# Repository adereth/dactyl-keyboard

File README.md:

# The Dactyl Keyboard
The Dactyl is a parameterized, split-hand, concave, columnar, ergonomic keyboard.

This is my fork of [the original Dactyl][], with rotated thumb clusters, a steeper angle, Ergodox-compatible keycaps, and a simpler one-piece chassis.

[the original Dactyl]: https://github.com/adereth/dactyl-keyboard

There's a talk about the motivation and design of the Dactyl that helps provide context for this repo:

## Assembly

### Generating a Design

**Setting up the Clojure environment**
* [Install the Clojure runtime](https://clojure.org)
* [Install the Leiningen project manager](http://leiningen.org/)
* [Install OpenSCAD](http://www.openscad.org/)

**Generating the design**
* Run `lein repl`
* Load the file `(load-file "src/dactyl_keyboard/dactyl.clj")`
* This will regenerate the `things/*.scad` files
* Use OpenSCAD to open a `.scad` file.
* Make changes to design, repeat `load-file`, OpenSCAD will watch for changes and rerender.
* When done, use OpenSCAD to export STL files

**Tips**
* [Some other ways to evaluate the clojure design file](http://stackoverflow.com/a/28213489)
* [Example designing with clojure](http://adereth.github.io/blog/2014/04/09/3d-printing-with-clojure/)

### Printing
Pregenerated STL files are available in the [things/](things/) directory.

### Wiring
Masks for the flexible PCBs I used are available for the [left](resources/pcb-left.svg) and [right](resources/pcb-right.svg) side.

A [very rough guide for the brave is here](guide/README.org#wiring) - It will be improved over time (**TODO**)!

## License

Copyright © 2015 Matthew Adereth

The source code for generating the models (everything excluding the [things/](things/) and [resources/](resources/) directories is distributed under the [GNU AFFERO GENERAL PUBLIC LICENSE Version 3](LICENSE).  The generated models and PCB designs are distributed under the [Creative Commons Attribution-ShareAlike License Version 4.0](LICENSE-models).

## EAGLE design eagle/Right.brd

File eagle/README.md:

# Eagle PCBs

These PCBs were designed to take the hastle out of wiring everything but the
switches. It's probably worth holding off on printing these until the case
accomodates them, they're tested, and we update the QMK guide for smooth
sailing.

# Ordering The Latest

| Board | OSH Park |
| ----- | -------- |
| Left v0.3 | <a href="https://oshpark.com/shared_projects/f4u5IMx5"></img></a> |
| Right v0.2 | <a href="https://oshpark.com/shared_projects/bUOCxaE4"></img></a> |

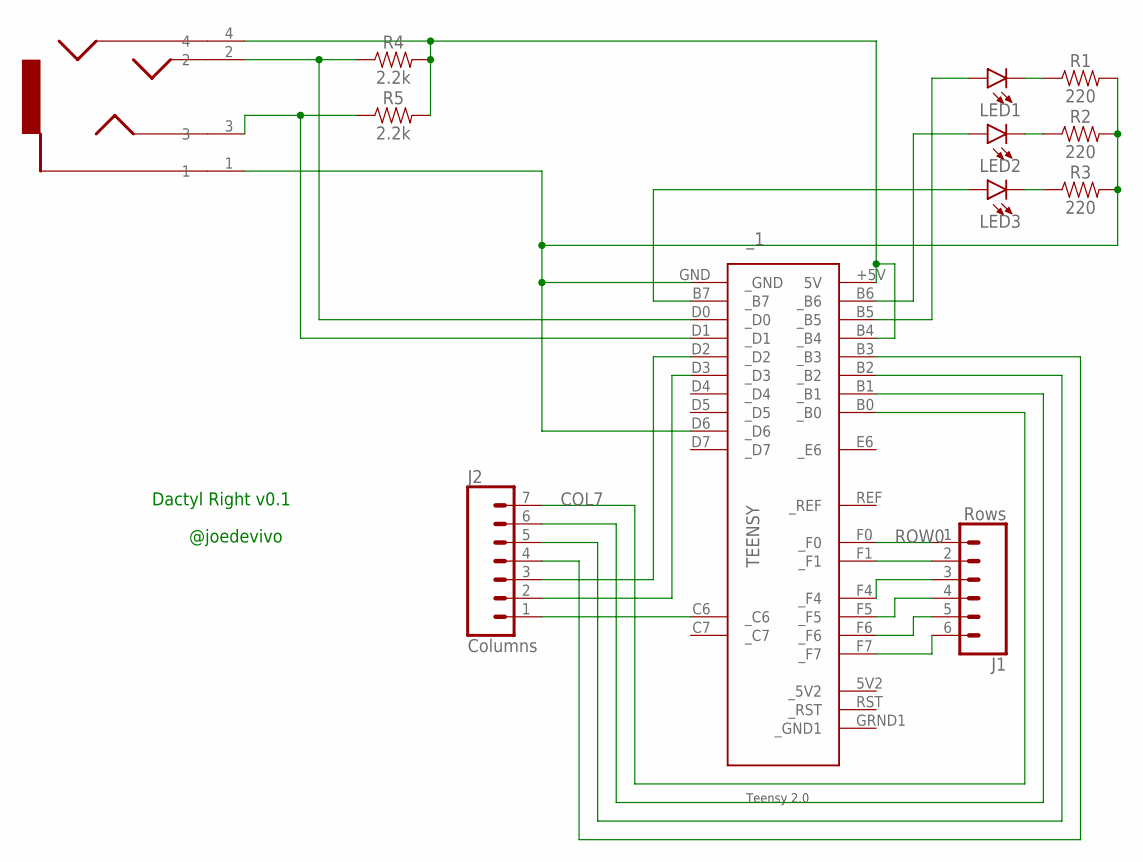
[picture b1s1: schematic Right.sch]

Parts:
J1: Rows; 1X06
J2: Columns; 1X07
LED1, LED2, LED3: LED3MM; LED_3MM
R1, R2, R3: 220; AXIAL-0.3
R4, R5: 2.2k; AXIAL-0.3
U$2: SJ-43514_HEADPHONES_3.5MM_X4; SJ-43514_HEADPHONES-3.5MM_X4
_1: TEENSY

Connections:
COL7: J2.7, _1.B0 (_B0)
unnamed: LED1.K (C), R1.P$1 (1)
unnamed: LED2.K (C), R2.P$1 (1)
unnamed: LED3.K (C), R3.P$1 (1)
unnamed: LED1.A, _1.B5 (_B5)
unnamed: LED2.A, _1.B6 (_B6)
unnamed: LED3.A, _1.B7 (_B7)
unnamed: R4.P$2 (2), R5.P$2 (2), U$2.4, _1.+5V (5V), _1.B4 (_B4)
unnamed: R4.P$1 (1), U$2.2, _1.D0 (_D0)
unnamed: R5.P$1 (1), U$2.3, _1.D1 (_D1)
unnamed: J2.2, _1.D3 (_D3)
unnamed: R1.P$2 (2), R2.P$2 (2), R3.P$2 (2), U$2.1, _1.D6 (_D6), _1.GND (_GND)
unnamed: J2.3, _1.D2 (_D2)
unnamed: J2.1, _1.C6 (_C6)
unnamed: J1.2, _1.F1 (_F1)
unnamed: J1.3, _1.F4 (_F4)
unnamed: J1.4, _1.F5 (_F5)
unnamed: J1.5, _1.F6 (_F6)
unnamed: J1.6, _1.F7 (_F7)
unnamed: J2.6, _1.B1 (_B1)
unnamed: J2.5, _1.B2 (_B2)
unnamed: J2.4, _1.B3 (_B3)
ROW0: J1.1, _1.F0 (_F0)

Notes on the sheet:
Dactyl Right v0.1
@joedevivo

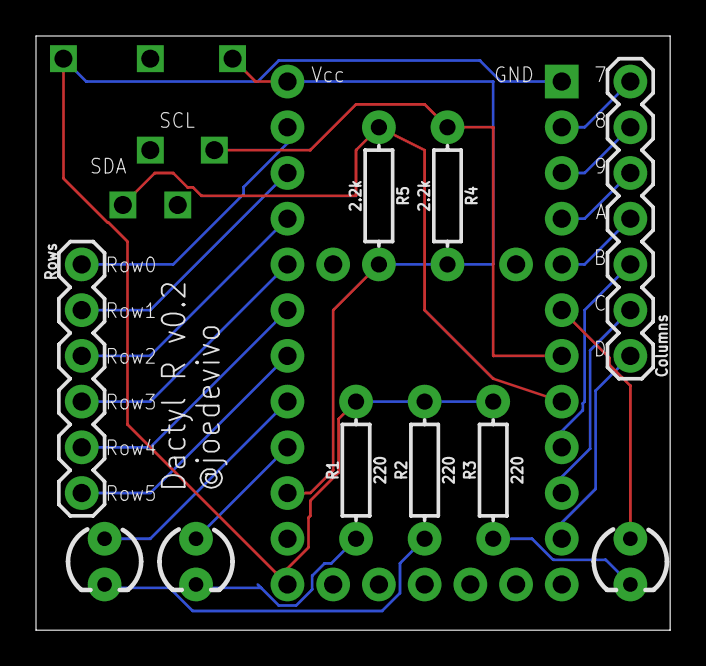
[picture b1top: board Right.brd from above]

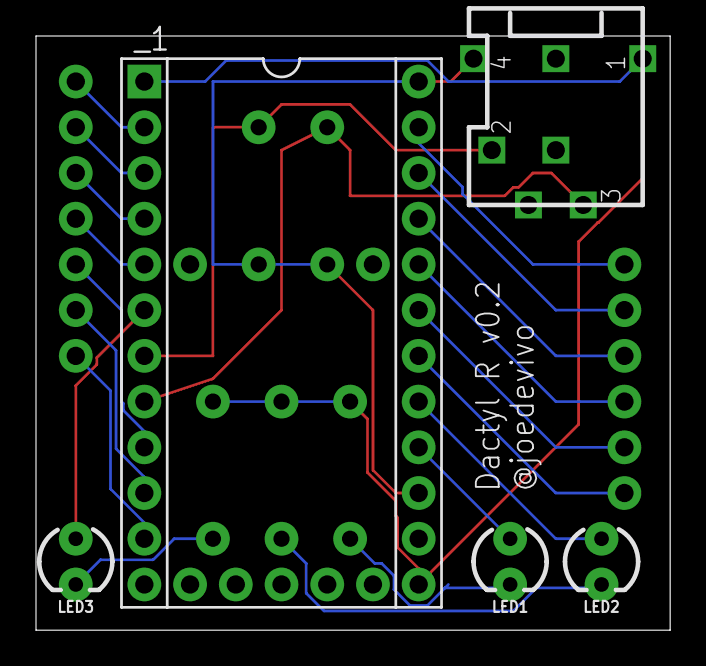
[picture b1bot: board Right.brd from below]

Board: 2 copper layers, 35.2 x 33.0 mm, 12 parts (5 on the bottom side), 23 nets.

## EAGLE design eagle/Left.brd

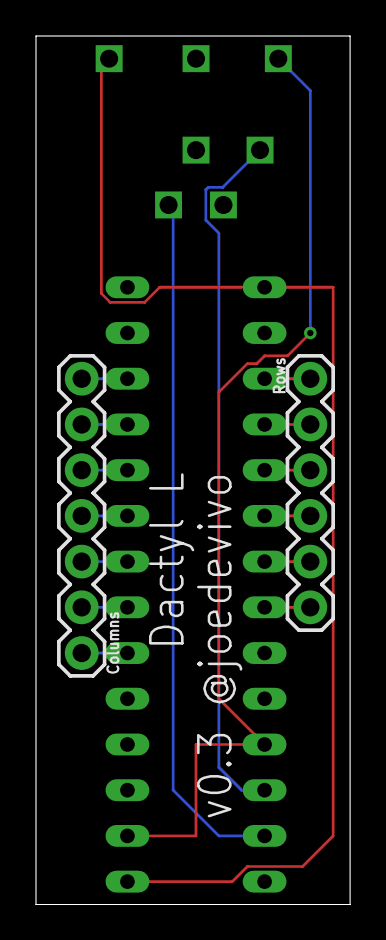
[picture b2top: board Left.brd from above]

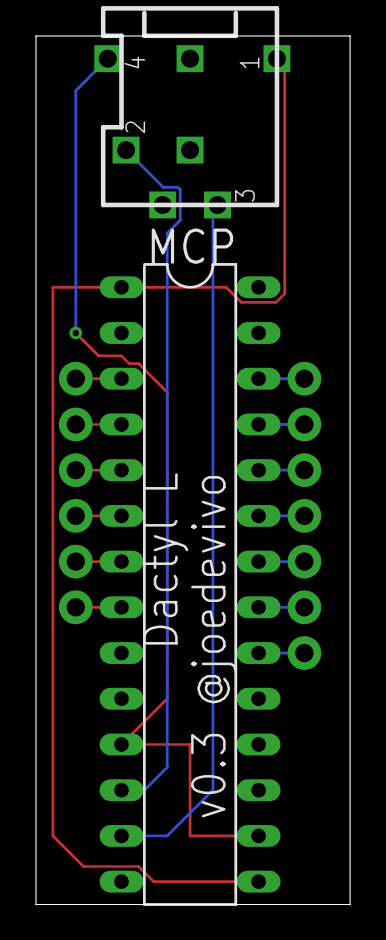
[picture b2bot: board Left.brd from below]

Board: 2 copper layers, 17.4 x 48.2 mm, 4 parts (2 on the bottom side), 17 nets.

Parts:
J1: Rows; 1X06
J2: Columns; 1X07
MCP: MCP23018SP; DIL28-3
U$1: SJ-43514_HEADPHONES_3.5MM_X4; SJ-43514_HEADPHONES-3.5MM_X4

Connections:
unnamed: MCP.1, MCP.15, U$1.1
unnamed: MCP.11, MCP.16, U$1.4
unnamed: MCP.13, U$1.3
unnamed: MCP.12, U$1.2
unnamed: J2.1, MCP.20
unnamed: J2.2, MCP.21
unnamed: J2.3, MCP.22
unnamed: J2.4, MCP.23
unnamed: J2.5, MCP.24
unnamed: J2.6, MCP.25
unnamed: J2.7, MCP.26
unnamed: J1.1, MCP.3
unnamed: J1.2, MCP.4
unnamed: J1.3, MCP.5
unnamed: J1.4, MCP.6
unnamed: J1.5, MCP.7
unnamed: J1.6, MCP.8

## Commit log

2015-03-06 Adding license
2015-03-06 Removing demo code
2015-03-13 Adding pregenerated thing files
2015-03-13 Adding one piece left hand
2015-03-13 Adding link to model from README
2015-03-13 Fixing link
2015-03-13 Adding pic
2015-03-13 Trying to get the pic to work
2015-12-02 New model!
2015-12-04 Finally sharing new model
2015-12-04 Updating licenses
2015-12-04 Including PCBs and updating README
2015-12-10 Add very rough guide
2015-12-27 Add to gitignore -- nrepl, lein, target cruft
2016-08-16 added to section Generating a Design
2016-08-16 had my links backwards
2016-08-16 downloading is implied
2016-09-06 initial commit after conversion with pandoc
2016-09-06 Added the Preparation and Cost section
2016-09-06 Added the wiring section
2016-09-06 makeup changes, replaced the 2 new pictures
2016-09-08 added the first part of route 2, creating the rows
2016-09-10 Route 2 upgraded
2016-09-10 improvements on Route 2
2016-09-11 Further upgrades on Route 2, diagrams added
2016-09-11 makeup changes
2016-10-10 Update link to README.org for wiring
2017-03-02 First try at manuform layout
2017-03-03 Close thumb shapes
2017-03-03 Connected thumb (mostly)
2017-03-04 Somewhat working side walls
2017-03-04 Completed case and filled in missing gaps
2017-03-04 Raise height
2017-03-05 Fix thin wall
2017-03-05 Fix border discontinuities
2017-03-05 Adjust height
2017-03-05 Tweaks; start usb cutout
2017-03-07 Height tweak
2017-03-07 First cut at on-wall-place
2017-03-07 Fix on-wall-rotation
2017-03-07 RJ9 holder
2017-03-08 Teensy holder
2017-03-08 Adding version with Teensy on left side
2017-03-09 merging
2017-03-10 Teensy hole and holder
2017-03-10 Move ManuForm changes to the main clj
2017-03-10 Readme updates and file reorg
2017-03-10 Quick and dirtly wrist rest
2017-03-10 Regenerated wrist
2017-03-10 Parameterizing updates
2017-03-11 Add hex spacers
2017-03-11 Tweak hex-spacer
2017-03-11 Adjust heights of the rj9 and teensy
2017-03-11 Fix readme
2017-03-11 Fix hex-spacers
2017-03-11 Add a test object for the hex spacers
2017-03-11 Add image of first print
2017-03-11 Another try at photo
2017-03-11 yet another photo try
2017-03-11 More photo tries
2017-03-11 Photo try
2017-03-11 Photo again
2017-03-12 Change hex spacers to better printing
2017-03-12 Kludgy maltron style spacing
2017-03-13 Thumb and pinky tweaks
2017-03-13 Fix keyboard-z-offset problem
2017-03-13 Tweaks for a shorter-height version
2017-03-13 Add wall-thickness parameter
2017-03-13 Teensy tweaks
2017-03-13 Various changes: * Change hex-spacers to screw-inserts * Adjust height * Fix usb-cutout size and alignment * Adjust teensy-holder
2017-03-13 Clean out junk
2017-04-01 Update LICENSE-models
2017-04-23 LightCycle with Cherry holes
2017-04-23 Adding Matias LightCycle
2017-04-23 Adding link to video
2017-04-23 Fixing left side with teensy, accidentally had ALPS switches
2017-05-19 Fixed TRRS cable name typo in README
    The word TRRS was misspelled as TTRS, making it difficult to identify this part.
2017-05-29 Sloppy LightCycle code
2017-06-08 [WIP] QMK Guide
2017-06-16 Fix MCP columns in wiring diagram
2017-06-16 Typo fix
2017-06-21 Remove columns 6 and 7
    I _think_ these columns came in from the ergodox circuit diagram.
    Compared to the dactyl, the ergodox has one extra column per hand (the
    three-key column at the middle).
2017-06-21 A bit more info about pull-up resistors
2017-06-21 Use .org link format, not markdown
    Oops :sweat:
2017-06-21 Fix spelling, grammar, and punctuation errors
2017-06-21 Remove "that's all for now" line
    There's a whole bunch of info after it! That clearly isn't all :)
2017-06-25 The pullups go to the I/O expander, not switches!
2017-06-26 Phat Dactyl & Ergo Dactyl
2017-06-26 Eagle PCB files
    While they're not tested yet, here they are as of the v0.2 run
2017-06-27 Added more to QMK guide
2017-07-13 v03 of Left board
2017-07-13 Added OSHPark links to eagle/README.md
2017-07-28 Return the MCP columns to GPA0-6
    Partially reverts 345b7eff270a579d889547b9b70f625c21d44412 .
    There had been a note that the columns actually went from INTA-GPA5.
    That's not right--although the firmware does write INTA during column
    operations, it's a control register, _not_ an I/O pin.
2017-08-01 Re-delete column 6
    It was removed in 976ca6903924e4fb5197cd6abf75ba24eec9028c (it only
    exists on the Ergodox), and accidentally restored in
    31ba812307e5f9b19649ac436c1d4f13f4e8f119.
2020-11-19 feat(dactyl.clj): tilted thumbs way down, similar to Manuform
2020-11-19 feat(dactyl.clj): invert 'column-radius' of thumb clusters to match natural thumb movement
    Apparently row/column are swapped when it comes to thumb clusters.
2020-11-21 Upgrade scad-clj
2020-11-21 feat(dactyl.clj):‌make 5th column 1.5-width keys
2020-11-21 feat(dactyl.clj): spit a "preview" model of the right side, with keycaps
2020-11-21 feat(dactyl.clj): rotate and raise the keys a bit more
    Reducing pronation.
2020-11-21 feat(dactyl.clj): added curtains around top piece instead of needing bottom
2020-11-21 feat(dactyl.clj): remove unnecessary screw holes
2020-11-21 feat(dactyl.clj):‌ don't generate bottom pieces
2020-11-21 fix(dactyl.clj): fixed seam in front curtain
2020-11-21 feat(dactyl.clj): move TRRS hole to the inside face
2020-11-22 fix(dactyl.clj):‌ correct diameter for my TRRS jacks
2020-11-22 feat(README.md):‌ updated description and screenshot for fork
2021-01-17 update lightcycle to only generate the switch holes
2021-01-17 top left things with only the switch openings

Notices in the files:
parts and their libraries:
SparkFun-Connectors: Licensing: Creative Commons ShareAlike 4.0 International - https://creativecommons.org/licenses/by-sa/4.0
teensy: Licensed Under Creative Commons Attribution-ShareAlike 3.0 Unported (CC BY-SA 3.0)
